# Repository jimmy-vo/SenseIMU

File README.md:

# SenseIMU
Control a mouse by human gesture via Bluetooth - A demonstration of Kalman Filter and other different optimization and estimation approaches.

## Input
* Accelerometer raw data
* Gyroscope raw data
* Magnetometer raw data

## Output
* Estimated Euler angles
* Estimated Quaternion set
* Represent object orientation on 3D Winform application
* Control mouse using estimated Euler angles via Bluetooth

## Functionality
* Bluetooth Connection
* Data plotting, 3D rendering
* Switching between different algorithms:
  - Tilt-compensation Method  
  - Gauss Newton Method 
  - AHRS
  - Quaternion based – gyro bias – EKF 
  - Quaternion based – gyro rate – EKF
  - DCM based KF 

## Screenshot

### HW Assembly  

### Demonstration

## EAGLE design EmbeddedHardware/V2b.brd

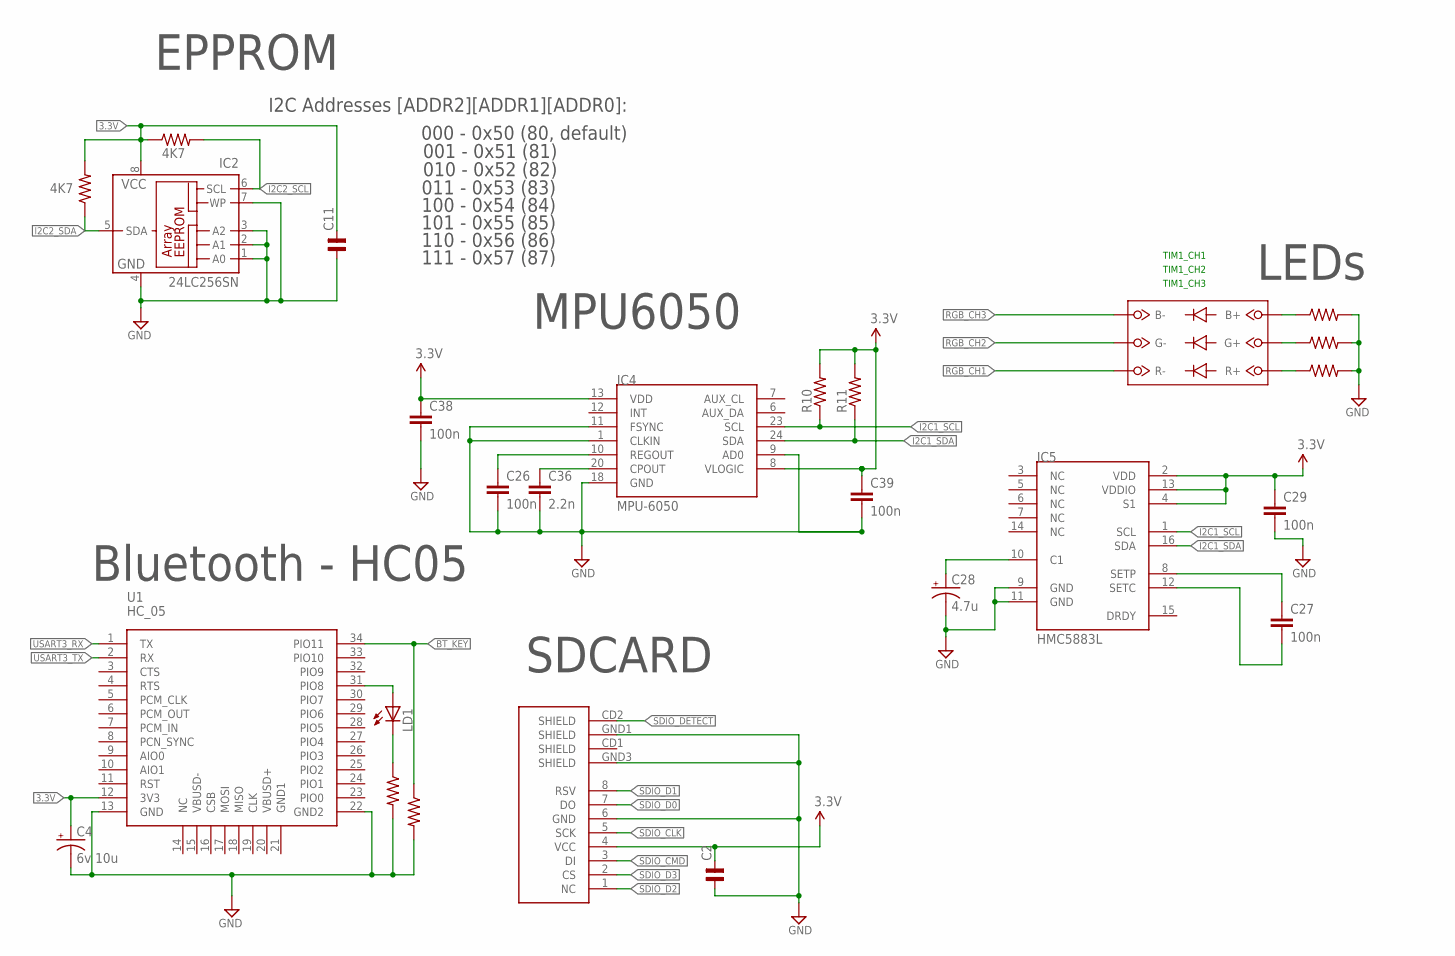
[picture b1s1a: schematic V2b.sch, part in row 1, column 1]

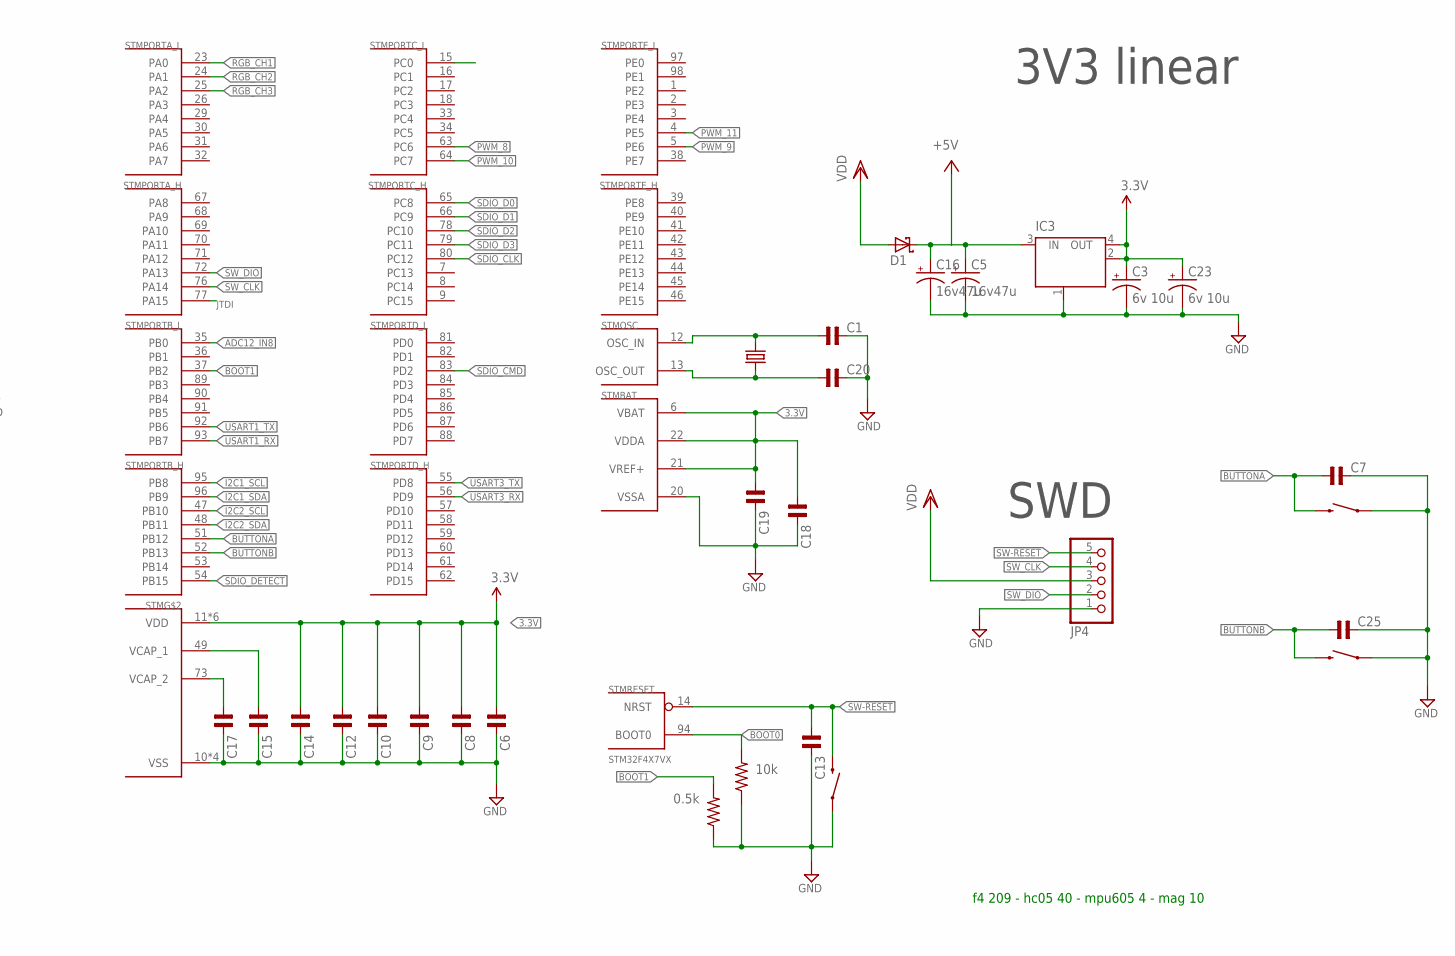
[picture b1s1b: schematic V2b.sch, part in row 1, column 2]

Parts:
C1, C2, C6, C7, C8, C9, C10, C11, C12, C13, C14, C15, C17, C18, C19, C20, C25: C-NP-SMD-0603; C-0603
C3, C23: 6v 10u; SMC_C
C4: 6v 10u; SMC_A
C5, C16: 16v47u; SMC_C
C26, C27, C29, C38, C39: 100n; SPARKFUN_0603-CAP
C28: 4.7u; SMC_A
C36: 2.2n; SPARKFUN_0603-CAP
D1: MBRS330T3; SMC
IC2: 24LC256SN; SO-08; DIGIKEY 24LC256-E/SN-ND
IC3: LINEAR_MC33269ST-3.3T3; LINEAR_SOT223
IC4: MPU-6050; TESTING_QFN-24-4MM2
IC5: HMC5883L; SPARKFUN_16LPCC
JP4: PINHD-1X5_2.54-90°; 1X05/90
LD1: LEDCHIPLED_0603; CHIPLED_0603
R2, R3, R5, R6, R9: 10K; SPARKFUN_0603-RES
R7: 10k; SPARKFUN_0603-RES
R8: 0.5k; SPARKFUN_0603-RES
R10, R11: SPARKFUN_RESISTOR0603-RES; SPARKFUN_0603-RES
R15, R16: 4K7; SPARKFUN_0603-RES
S1, S2, S4: RESET; TACTILE-SWITCH-1101NE; PARTNO EVQ-P7J01P
SDCARD2: microSD Socket; MICRO-SD-SOCKET-PP
STM: STM32F4X7VX; TQFP100; PARTNO STM32F427VI
U1: HC_05; BLUETOOTH_SMD
U$12: RGB_LED; SMD
Y1: CRYSTALHC49US; HC49US

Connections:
3.3V: C2.2, C3.+, C4.+, C6.1, C8.1, C9.1, C10.1, C11.2, C12.1, C14.1, C18.1, C19.1, C23.+, C29.1, C38.1, C39.1, IC2.8 (VCC), IC3.2 (OUT), IC3.4 (OUT), IC4.8 (VLOGIC), IC4.13 (VDD), IC5.2 (VDD), IC5.4 (S1), IC5.13 (VDDIO), R10.2, R11.2, R15.1, R16.2, SDCARD2.4 (VCC), STM.6 (VBAT), STM.11 (VDD), STM.19 (VDD), STM.21 (VREF+), STM.22 (VDDA), STM.28 (VDD), STM.50 (VDD), STM.75 (VDD), STM.100 (VDD), U1.12 (3V3)
+5V: C5.+, C16.+, D1.C, IC3.3 (IN)
ADC12_IN8: STM.35 (PB0)
BOOT0: R7.2, STM.94 (BOOT0)
BOOT1: R8.2, STM.37 (PB2)
BT_KEY: R5.1, U1.34 (PIO11)
BUTTONA: C7.1, S4.P$2 (2), STM.51 (PB12)
BUTTONB: C25.1, S2.P$2 (2), STM.52 (PB13)
GND: C1.2, C2.1, C3.-, C4.-, C5.-, C6.2, C7.2, C8.2, C9.2, C10.2, C11.1, C12.2, C13.2, C14.2, C15.2, C16.-, C17.2, C18.2, C19.2, C20.2, C23.-, C25.2, C26.2, C28.-, C29.2, C36.2, C38.2, C39.2, IC2.1 (A0), IC2.2 (A1), IC2.3 (A2), IC2.4 (GND), IC2.7 (WP), IC3.1 (GND/ADJ), IC4.1 (CLKIN), IC4.9 (AD0), IC4.11 (FSYNC), IC4.18 (GND), IC5.9 (GND), IC5.11 (GND), JP4.1, R2.2, R3.2, R5.2, R6.2, R7.1, R8.1, R9.2, S1.P$1 (1), S2.P$1 (1), S4.P$1 (1), SDCARD2.6 (GND), SDCARD2.GND1 (SHIELD), SDCARD2.GND3 (SHIELD), STM.10 (VSS), STM.20 (VSSA), STM.27 (VSS), STM.74 (VSS), STM.99 (VSS), U1.13 (GND), U1.22 (GND2)
I2C1_SCL: IC4.23 (SCL), IC5.1 (SCL), R10.1, STM.95 (PB8)
I2C1_SDA: IC4.24 (SDA), IC5.16 (SDA), R11.1, STM.96 (PB9)
I2C2_SCL: IC2.6 (SCL), R15.2, STM.47 (PB10)
I2C2_SDA: IC2.5 (SDA), R16.1, STM.48 (PB11)
JTDI: STM.77 (PA15)
unnamed: C1.1, STM.12 (OSC_IN), Y1.2
unnamed: R2.1, U$12.B+
unnamed: C26.1, IC4.10 (REGOUT)
unnamed: LD1.A, U1.31 (PIO8)
unnamed: LD1.C, R9.1
unnamed: R6.1, U$12.R+
unnamed: R3.1, U$12.G+
unnamed: C36.1, IC4.20 (CPOUT)
unnamed: C27.1, IC5.8 (SETP)
unnamed: C28.+, IC5.10 (C1)
unnamed: C27.2, IC5.12 (SETC)
unnamed: C20.1, STM.13 (OSC_OUT), Y1.1
unnamed: C17.1, STM.73 (VCAP_2)
unnamed: C15.1, STM.49 (VCAP_1)
PWM_8: STM.63 (PC6)
PWM_9: STM.5 (PE6)
PWM_10: STM.64 (PC7)
PWM_11: STM.4 (PE5)
RGB_CH1: STM.23 (PA0), U$12.R-
RGB_CH2: STM.24 (PA1), U$12.G-
RGB_CH3: STM.25 (PA2), U$12.B-
SDIO_CLK: SDCARD2.5 (SCK), STM.80 (PC12)
SDIO_CMD: SDCARD2.3 (DI), STM.83 (PD2)
SDIO_D0: SDCARD2.7 (DO), STM.65 (PC8)
SDIO_D1: SDCARD2.8 (RSV), STM.66 (PC9)
SDIO_D2: SDCARD2.1 (NC), STM.78 (PC10)
SDIO_D3: SDCARD2.2 (CS), STM.79 (PC11)
SDIO_DETECT: SDCARD2.CD2 (SHIELD), STM.54 (PB15)
SW-!RESET: C13.1, JP4.5, S1.P$2 (2), STM.14 (NRST)
SW_CLK: JP4.4, STM.76 (PA14)
SW_DIO: JP4.2, STM.72 (PA13)
USART1_RX: STM.93 (PB7)
USART1_TX: STM.92 (PB6)
USART3_RX: STM.56 (PD9), U1.1 (TX)
USART3_TX: STM.55 (PD8), U1.2 (RX)
VDD: D1.A, JP4.3

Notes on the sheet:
SWD
LEDs
TIM1_CH1
TIM1_CH2
TIM1_CH3
I2C Addresses [ADDR2][ADDR1][ADDR0]:
000 - 0x50 (80, default)
001 - 0x51 (81)
010 - 0x52 (82)
011 - 0x53 (83)
100 - 0x54 (84)
101 - 0x55 (85)
110 - 0x56 (86)
111 - 0x57 (87)
EPPROM
Bluetooth - HC05
SDCARD
3V3 linear
MPU6050
f4 209 - hc05 40 - mpu605 4 - mag 10

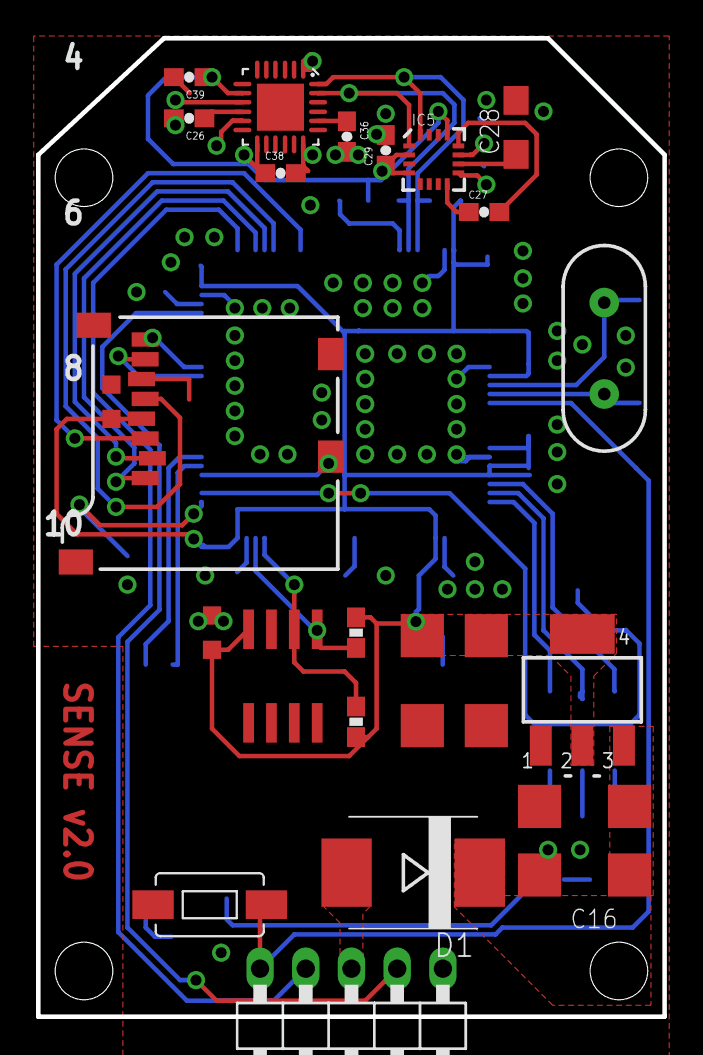
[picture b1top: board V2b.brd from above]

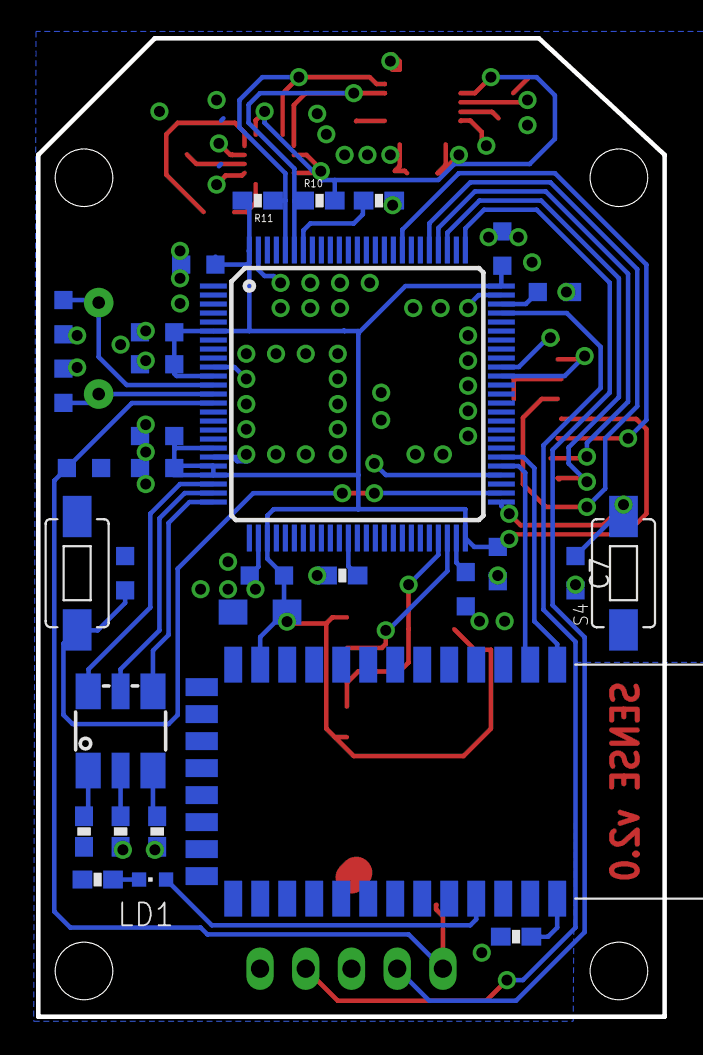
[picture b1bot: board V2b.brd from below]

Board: 2 copper layers, 34.8 x 54.4 mm, 55 parts (31 on the bottom side), 42 nets.

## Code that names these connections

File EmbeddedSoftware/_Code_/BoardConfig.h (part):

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#define I2C1_GPIO_CLK						RCC_AHB1Periph_GPIOB
#define I2C1_AF									GPIO_AF_I2C1

#define I2C1_SCL_PIN						GPIO_Pin_8
#define I2C1_SCL_SOURCE					GPIO_PinSource8
#define I2C1_SDA_PIN						GPIO_Pin_9
#define I2C1_SDA_SOURCE					GPIO_PinSource9

#define I2C1_RX_DMA_CH					DMA_Channel_1
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#define I2C2_GPIO_CLK						RCC_AHB1Periph_GPIOB
#define I2C2_AF									GPIO_AF_I2C2

#define I2C2_SCL_PIN						GPIO_Pin_10
#define I2C2_SCL_SOURCE					GPIO_PinSource10
#define I2C2_SDA_PIN						GPIO_Pin_11
#define I2C2_SDA_SOURCE					GPIO_PinSource11

#define I2C2_RX_DMA_CH					DMA_Channel_7
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  /////////////////////////////////////////////////////////////////
 //														SD CARD														//									
/////////////////////////////////////////////////////////////////
#define SDIO_CLK								RCC_APB2Periph_SDIO

#define SDIO_GPIO_DETECT_PORT		GPIOB
#define SDIO_GPIO_DETECT_CLK		RCC_AHB1Periph_GPIOB
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
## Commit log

2018-03-03 upload
2018-03-04 upload images

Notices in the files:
parts and their libraries:
SparkFun-FreqCtrl: Licensing: CC v3.0 Share-Alike You are welcome to use this library for commercial purposes.
cap-pan40: Copyright (C) 2004, Bob Starr
